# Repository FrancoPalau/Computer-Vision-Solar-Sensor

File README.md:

# Solar Tracker with Computer-Vision Solar Sensor

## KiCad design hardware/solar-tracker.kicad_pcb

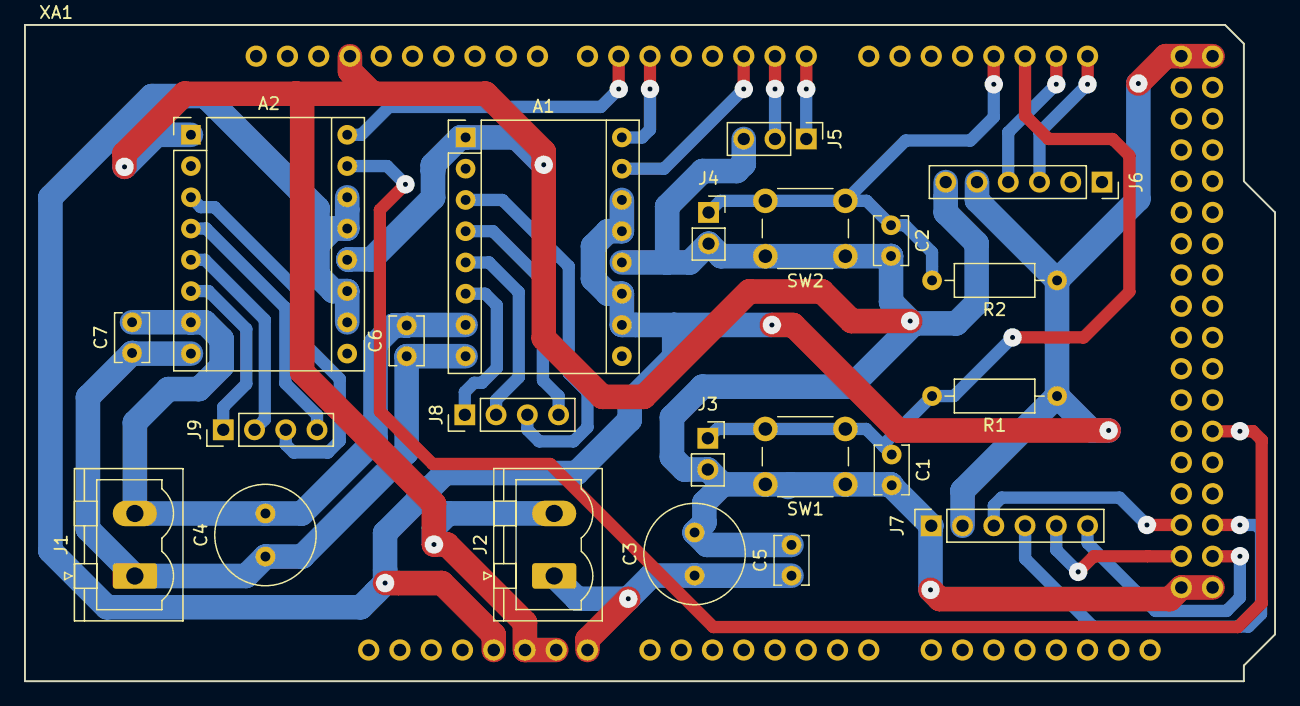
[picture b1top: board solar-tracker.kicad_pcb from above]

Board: 2 copper layers, 101.6 x 53.3 mm, 23 parts (0 on the bottom side), 27 nets.

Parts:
A1, A2: Pololu DRV8825; Pololu_Breakout-16_15.2x20.3mm
C1, C2, C5, C6, C7: 0.1uF; C_Disc_D3.8mm_W2.6mm_P2.50mm
C3, C4: 100uF; C_Radial_D8.0mm_H11.5mm_P3.50mm
J1: 12V Power; PhoenixContact_MSTBVA_2,5_2-G-5,08_1x02_P5.08mm_Vertical
J2: 5V Power; PhoenixContact_MSTBVA_2,5_2-G-5,08_1x02_P5.08mm_Vertical
J3: Limit Switch A; PinSocket_1x02_P2.54mm_Vertical
J4: Limit Switch B; PinSocket_1x02_P2.54mm_Vertical
J5: Serial Communication; PinHeader_1x03_P2.54mm_Vertical
J6: microSD Module; PinSocket_1x06_P2.54mm_Vertical
J7: RTC Module; PinSocket_1x06_P2.54mm_Vertical
J8: STEPPER A; PinHeader_1x04_P2.54mm_Vertical
J9: STEPPER B; PinHeader_1x04_P2.54mm_Vertical
R1, R2: 4.7K; R_Axial_DIN0207_L6.3mm_D2.5mm_P10.16mm_Horizontal
SW1, SW2: SW_Push; SW_PUSH_6mm
XA1: Arduino Mega2560 Shield; Arduino_Mega2560_Shield

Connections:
+5V: A1.10, A1.11, A1.13, A1.14, A2.10, A2.11, A2.13, A2.14, J6.5, J7.2, R1.1, R2.1, XA1.5V1, XA1.5V3, XA1.5V4
DIR_A: A1.16, XA1.D5
DIR_B: A2.16, XA1.D6
GND: A1.7, A2.7, C4.2, C6.2, C7.2, J1.2
GNDD: A1.1, A1.12, A2.1, A2.12, C1.2, C2.2, C3.2, C5.2, J2.2, J3.2, J4.2, J5.3, J6.6, J7.1, SW1.1, SW2.1, XA1.GND1, XA1.GND2, XA1.GND3, XA1.GND5, XA1.GND6
LIM_A: C1.1, J3.1, R1.2, SW1.2, XA1.D19
LIM_B: C2.1, J4.1, R2.2, SW2.2, XA1.D18
unnamed: A1.3, J8.3
unnamed: A1.4, J8.4
unnamed: A1.5, J8.2
unnamed: A1.6, J8.1
unnamed: A2.3, J9.3
unnamed: A2.4, J9.4
unnamed: A2.5, J9.2
unnamed: A2.6, J9.1
unnamed: J5.1, XA1.D0
unnamed: J5.2, XA1.D1
unnamed: J6.3, XA1.D21
unnamed: J6.4, XA1.D20
unnamed: J7.3, XA1.D50
unnamed: J7.4, XA1.D51
unnamed: J7.5, XA1.D52
unnamed: J7.6, XA1.D53
STEP_A: A1.15, XA1.D2
STEP_B: A2.15, XA1.D45
VIN: C3.1, C5.1, J2.1, XA1.VIN
VMOT_A: A1.8, A2.8, C4.1, C6.1, C7.1, J1.1

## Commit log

2018-08-20 Primer commit
2018-08-20 Draw axis and distances
2018-08-20 test with static image
2019-01-25 Detection circle working
2019-01-25 Add serial module and logic
2019-01-26 serial module working
2019-01-26 add functions to draw on image
2019-01-28 fix bug in distance calculation
2019-01-28 add files for the solar-tracker control
2019-01-28 add solar-sensor folder
2019-01-28 fix folder problem
2019-01-29 fix bug sending the corresponding axis signal
2019-01-31 add switch case for UART
2019-01-31 Add sensor status flag
2019-01-31 Fix problem with variable pe increasing non-stop
2019-02-01 Add atomic block to stop interruptions during movement of motor
2019-02-03 add logic to send only one axis query per cycle
2019-05-10 main modified not working
2019-05-11 fixed bug issue #3
2019-05-15 serial communication working
2019-05-26 added hardware folder with fritzing files and README update
2019-07-05 added kicad schematic scketch with mega, drivers and buttons connections
2019-07-05 added kicad schematic microsd adapter and rtc
2019-07-05 added 3d model and pcbnew scketch
2019-07-05 added 3d view and schematic with all connectors
2019-07-30 new comments in main and timers
2019-07-30 posible error en declaración de pin para timer 5
2019-08-07 added first steps in the process from arduino to rpi3, stepper utils
2019-08-17 added input to hardware module and test
2019-08-17 added limit switch setup
2019-08-17 added homing module and fixes in hardware
2019-08-17 added and fixed comments
2019-08-17 added main with homing
2019-08-17 added old generarNombre function
2019-08-18 deleted i2c and rtc
2019-08-18 fixed python version compatibility issues
2019-08-18 added time handling process
2019-08-18 added data and time processes
2019-08-18 added sequential homing process
2019-08-30 added C fixes after avr-to-rpi
2019-08-30 added changes to data_handling (need review)
2019-08-30 several changes, no needed files (need review)
2019-08-30 rm test.c
2019-08-30 rm build files
2019-08-30 rm extra C files
2019-08-30 fixed hw logic bugs and added external interruptions
2019-08-30 fixed time handling process bug
2019-08-31 added image processing tools
2019-09-08 rm several prints
2019-09-19 harware update
2019-09-20 update pcb con agujeros no conductores
2019-09-21 update pcb pistas más anchas
2019-09-23 added eesquema v1.0
2019-09-23 new pcb iteration more C other power conn
2019-09-23 pcb new connectors for stepper
2019-09-23 added eesquema in README
2019-09-23 resize eesquema in README
2019-09-23 cut eesquema in README
2020-02-29 added conda environment.yml
2020-03-02 general update (ponele)
2021-06-25 Prueba de acceso
2021-07-05 workspace added ROS proyect
2021-07-12 added time data files
2021-07-15 State Machine Added
2021-08-18 Machine Satates Added. Main system working.
2021-08-27 Optimizacion de maquina de estado,lanzador launch
2022-03-04 stepper controller ROS
